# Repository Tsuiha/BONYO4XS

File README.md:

# BONYO4XS

　BONYO4XSは40%サイズの分割キーボードです。
 
　リポジトリに設計データが公開されています。 自由にしてください。

　[noteでも紹介しています](https://note.com/tsuiha/m/m1388ad3cf830)

 片側4x6の計48キーを搭載しているカラムスタッガード（小指列が0.25U下がったオーソリニア）配列です。

 　サンドイッチマウント構造で、デフォルト10mm程度のテンティングが施されています。
　奥側のゴム足に高さのあるものを使用することでチルト＋テントの状態で使用することができ、手の姿勢が気持ちよく打鍵できると感じています。

 　親指4キー分のサムクラスタはMXキースイッチだけでなく、プレートを分離することでChoc V2キースイッチにも対応することができます。

 　親指キーにロープロファイルスイッチを使用することで、テンティング時の親指キー高さが気になりにくくなります。

   外観写真

   ## ビルドガイド

使用部品はparts listを参照ください。

　実装用基板、スイッチプレート、ボトムプレート、テントプレートの4種が含まれています。
　ラジオペンチ等でランナーを除去し、バリをやすり等で削ります。

　画像を参考に基板に部品を実装します。左右と表裏に注意して進めます。

（下面赤枠）
　ダイオードを24か所に実装します。部品が下面に来るように実装します。画像ではDIPタイプを使用していますが、SMDタイプも使用できます。ダイオードには向きがあります。

（上面赤枠）
　上面の指定7箇所のみをジャンパします。

（下面青枠）
　TRSジャックを部品が下面に来るように実装します。

（下面緑枠）
　ロープロピンソケットを部品が下面に来るように実装します。*マイコンボードと一緒に実装するため、部品実装・マイコンボード項に従ってください。

部品実装・マイコンボード  
　マイコンボード - ピンヘッダ - ピンソケット - 基板 すべて重ねた状態ではんだ付けを行います。これは後にマイコンボードを容易に取り外せるようにするためです

部品実装・キースイッチ  
左側を例に進めます。

　スイッチプレートにキースイッチをはめこみます。
　*このときChoc V2を使用する際は、スリット部を切断しChoc V2キースイッチをはめてください。

　8mmスペーサを6か所ねじ止めします。
　*このときChoc V2を使用する際は、親指部に5mmスペーサを使用してください。

ボトムプレートとテントプレートで8mmスペーサを挟み。両側から2か所ねじ止めします。

　マイコンボードを再度基板に装着します。
　基板側とボトムプレート側を重ね、下面から6か所ねじ止めします。

 完成です。

## qmk-vial
　ファームウェアにはqmk-vialを使用しています。

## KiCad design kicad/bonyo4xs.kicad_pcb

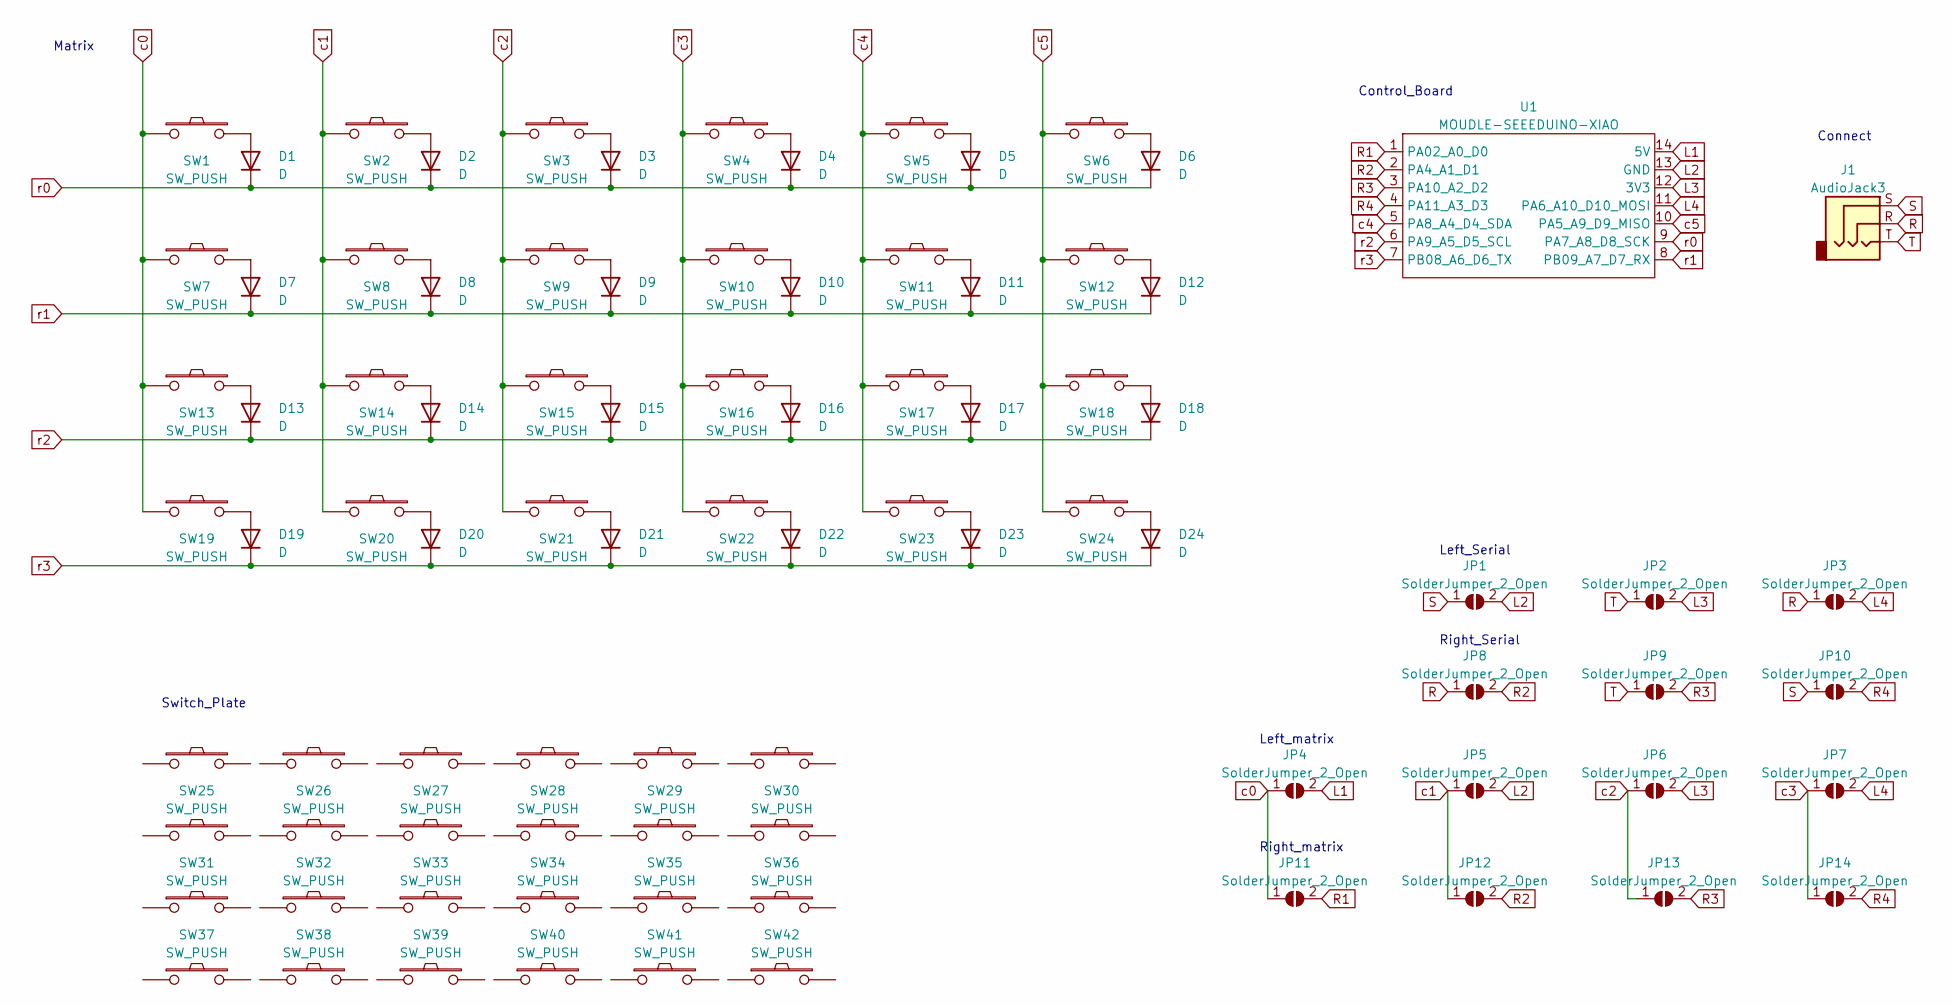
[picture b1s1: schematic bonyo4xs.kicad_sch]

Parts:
D1, D2, D3, D4, D5, D6, D7, D8, D9, D10, D11, D12, D13, D14, D15, D16, D17, D18, D19, D20, D21, D22, D23, D24: D; D3_TH_SMD
J1: AudioJack3; Jack_3.5mm_Switronic_ST-005-G_horizontal_maru
JP1, JP2, JP3, JP4, JP5, JP6, JP7, JP8, JP9, JP10, JP11, JP12, JP13, JP14: SolderJumper_2_Open; jamp_2
SW1, SW2, SW3, SW4, SW5, SW6, SW7, SW8, SW9, SW10, SW11, SW12, SW13, SW14, SW15, SW16, SW17, SW18, SW19, SW20: SW_PUSH; CherryMX_1u_nofix_rev
SW21, SW22, SW23, SW24: SW_PUSH; CherryMX_ChocV2_1u_nofix
SW25, SW26, SW27, SW28, SW29, SW30, SW31, SW32, SW33, SW34, SW35, SW36, SW37, SW38, SW39, SW40, SW41, SW42, SW43, SW44, SW45, SW46, SW47, SW48: SW_PUSH; SW_Hole_1u
U1: MOUDLE-SEEEDUINO-XIAO; MOUDLE14P-2.54-21X17.8MM

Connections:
L1: JP4.2 (B), U1.14 (5V)
L2: JP1.2 (B), JP5.2 (B), U1.13 (GND)
L3: JP2.2 (B), JP6.2 (B), U1.12 (3V3)
L4: JP3.2 (B), JP7.2 (B), U1.11 (PA6_A10_D10_MOSI)
unnamed: D1.2 (A), SW1.2
unnamed: D2.2 (A), SW2.2
unnamed: D3.2 (A), SW3.2
unnamed: D4.2 (A), SW4.2
unnamed: D5.2 (A), SW5.2
unnamed: D6.2 (A), SW6.2
unnamed: D7.2 (A), SW7.2
unnamed: D8.2 (A), SW8.2
unnamed: D9.2 (A), SW9.2
unnamed: D10.2 (A), SW10.2
unnamed: D11.2 (A), SW11.2
unnamed: D12.2 (A), SW12.2
unnamed: D13.2 (A), SW13.2
unnamed: D14.2 (A), SW14.2
unnamed: D15.2 (A), SW15.2
unnamed: D16.2 (A), SW16.2
unnamed: D17.2 (A), SW17.2
unnamed: D18.2 (A), SW18.2
unnamed: D19.2 (A), SW19.2
unnamed: D20.2 (A), SW20.2
unnamed: D21.2 (A), SW21.2
unnamed: D22.2 (A), SW22.2
unnamed: D23.2 (A), SW23.2
unnamed: D24.2 (A), SW24.2
R: J1.R, JP3.1 (A), JP8.1 (A)
R1: JP11.2 (B), U1.1 (PA02_A0_D0)
R2: JP8.2 (B), JP12.2 (B), U1.2 (PA4_A1_D1)
R3: JP9.2 (B), JP13.2 (B), U1.3 (PA10_A2_D2)
R4: JP10.2 (B), JP14.2 (B), U1.4 (PA11_A3_D3)
S: J1.S, JP1.1 (A), JP10.1 (A)
T: J1.T, JP2.1 (A), JP9.1 (A)
c0: JP4.1 (A), JP11.1 (A), SW1.1, SW7.1, SW13.1, SW19.1
c1: JP5.1 (A), JP12.1 (A), SW2.1, SW8.1, SW14.1, SW20.1
c2: JP6.1 (A), JP13.1 (A), SW3.1, SW9.1, SW15.1, SW21.1
c3: JP7.1 (A), JP14.1 (A), SW4.1, SW10.1, SW16.1, SW22.1
c4: SW5.1, SW11.1, SW17.1, SW23.1, U1.5 (PA8_A4_D4_SDA)
c5: SW6.1, SW12.1, SW18.1, SW24.1, U1.10 (PA5_A9_D9_MISO)
r0: D1.1 (K), D2.1 (K), D3.1 (K), D4.1 (K), D5.1 (K), D6.1 (K), U1.9 (PA7_A8_D8_SCK)
r1: D7.1 (K), D8.1 (K), D9.1 (K), D10.1 (K), D11.1 (K), D12.1 (K), U1.8 (PB09_A7_D7_RX)
r2: D13.1 (K), D14.1 (K), D15.1 (K), D16.1 (K), D17.1 (K), D18.1 (K), U1.6 (PA9_A5_D5_SCL)
r3: D19.1 (K), D20.1 (K), D21.1 (K), D22.1 (K), D23.1 (K), D24.1 (K), U1.7 (PB08_A6_D6_TX)

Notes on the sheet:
Left_Serial
Right_matrix
Left_matrix
Right_Serial
Switch_Plate
Control_Board
Matrix
Connect

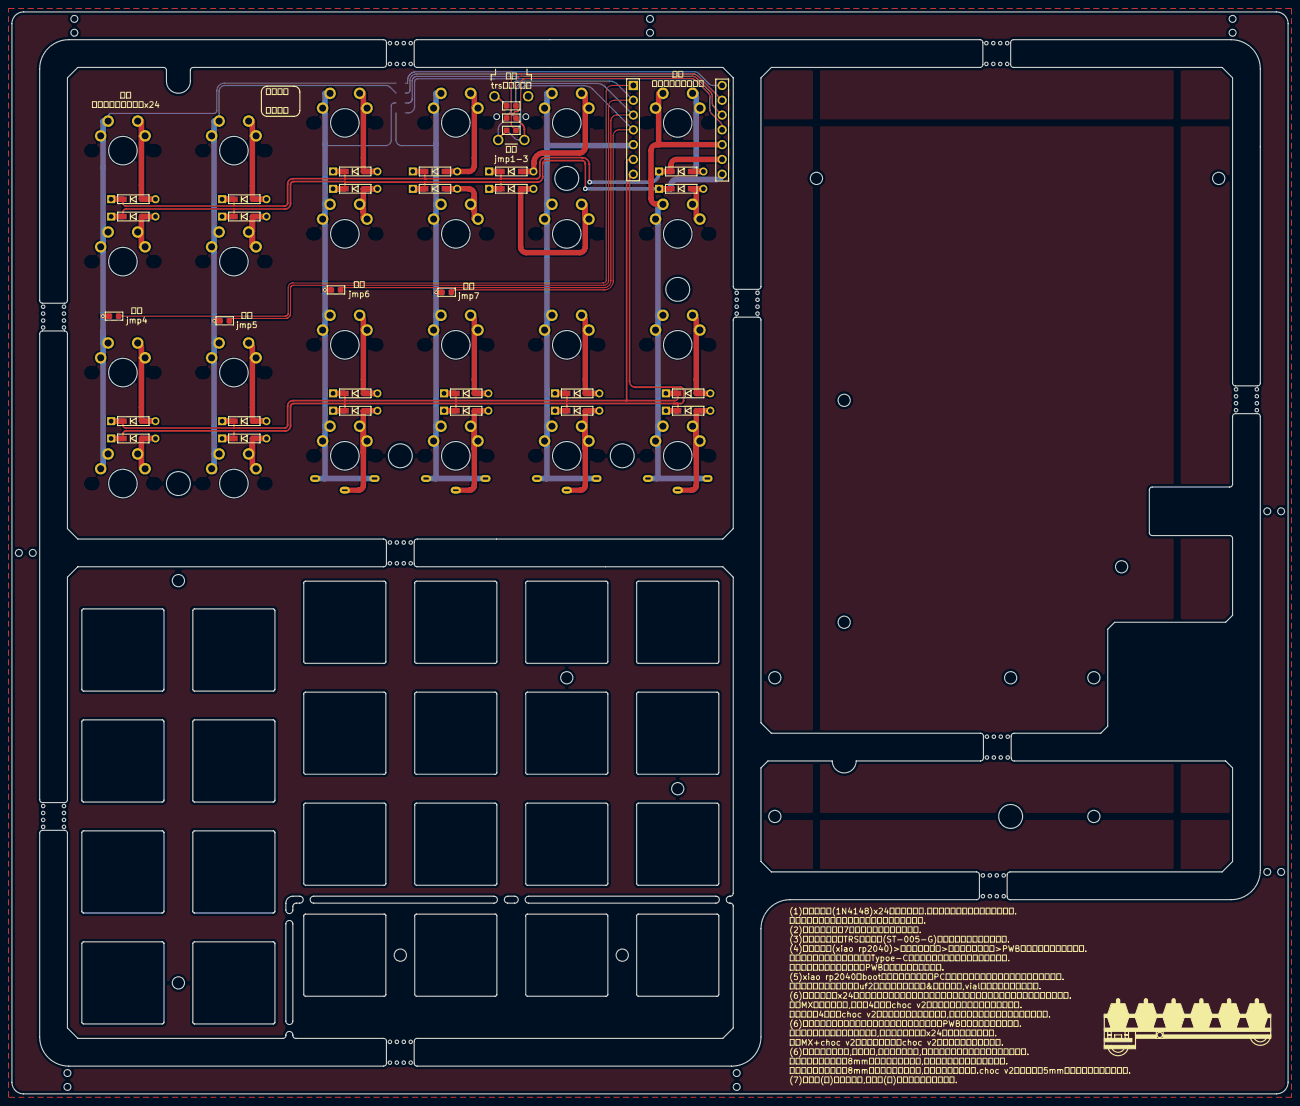
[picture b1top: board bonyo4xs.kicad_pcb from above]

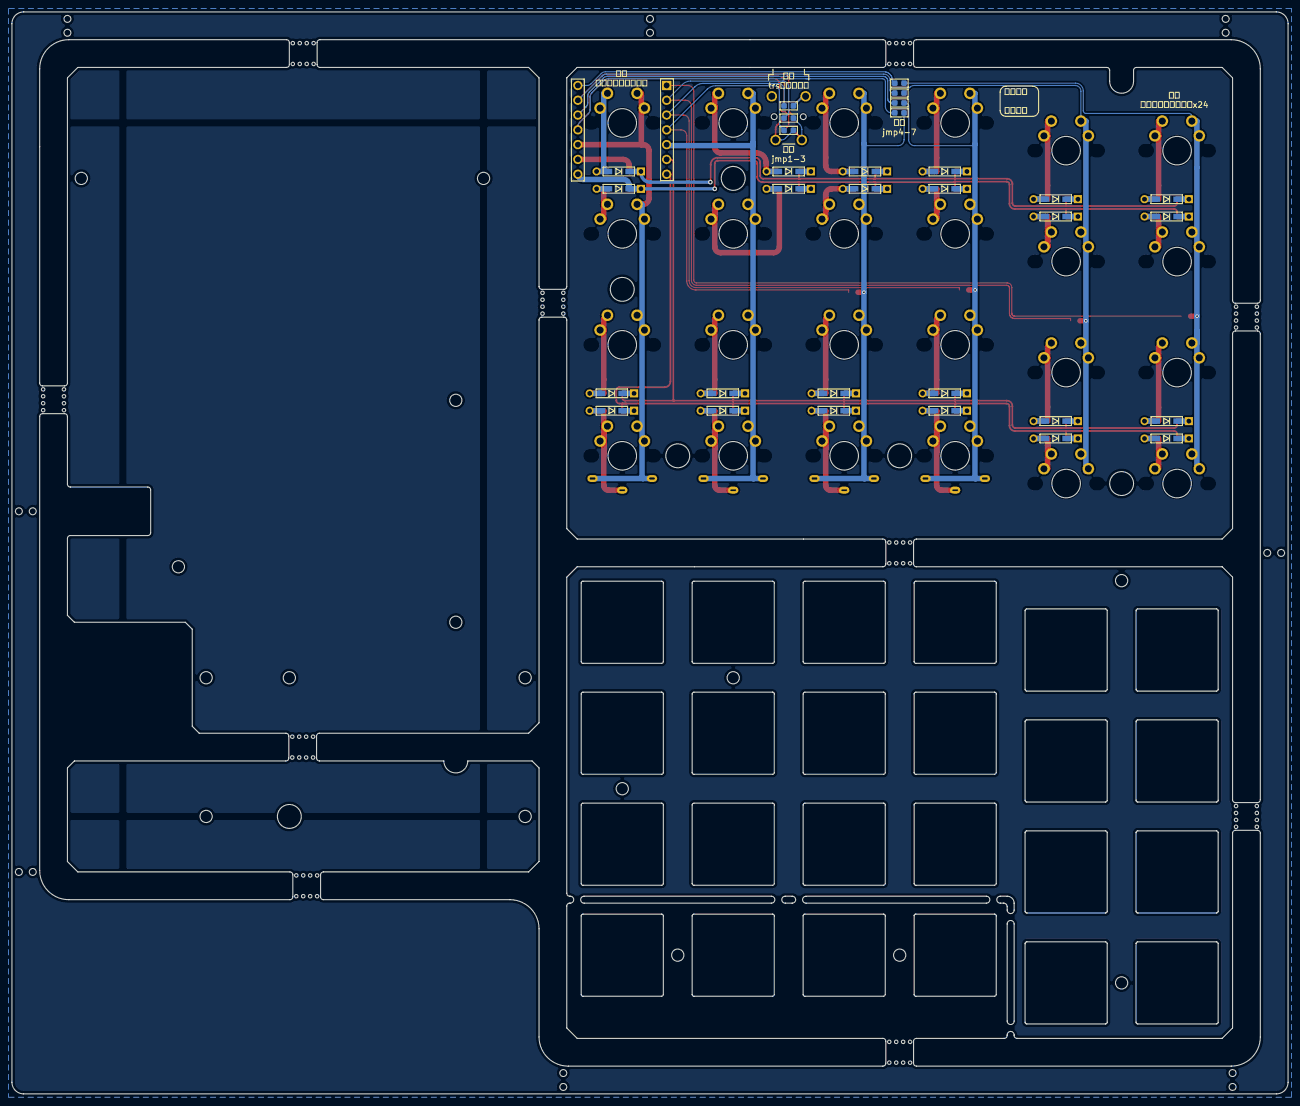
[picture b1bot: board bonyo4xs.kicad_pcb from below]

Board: 2 copper layers, 219.1 x 185.7 mm, 88 parts (32 on the bottom side), 45 nets.

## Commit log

2025-03-03 Create LICENSE
